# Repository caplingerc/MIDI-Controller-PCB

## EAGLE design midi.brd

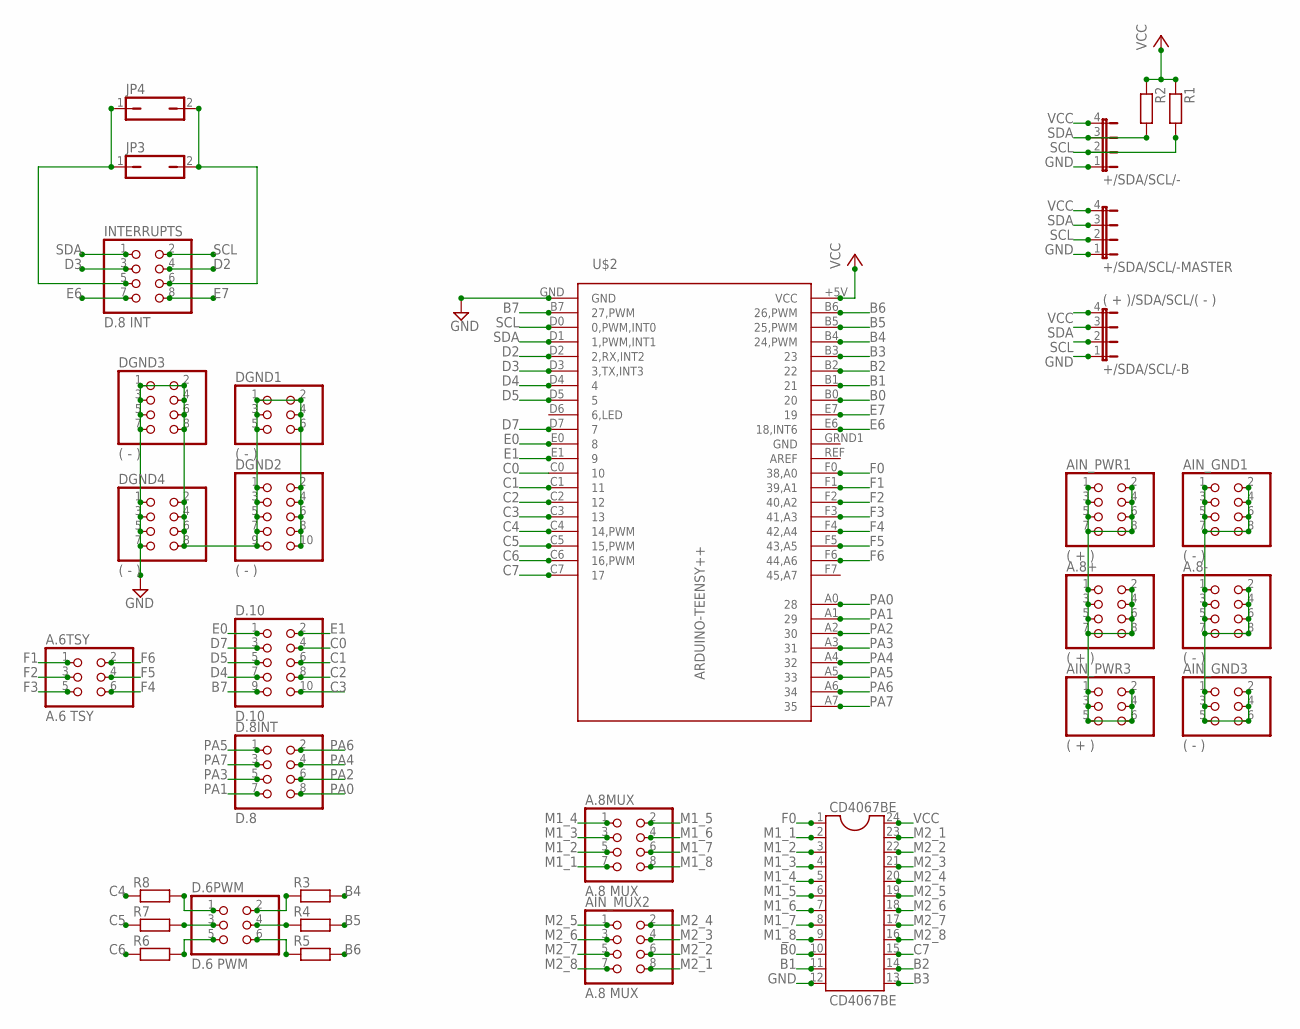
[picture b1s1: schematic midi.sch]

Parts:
+/SDA/SCL/-: JP4E; JP4
+/SDA/SCL/-B: ( + )/SDA/SCL/( - ); JP4
+/SDA/SCL/-MASTER: JP4E; JP4
A.6TSY: A.6 TSY; 2X03
A.8+: ( + ); 2X04
A.8-: ( - ); 2X04
A.8MUX: A.8 MUX; 2X04
AIN_GND1: ( - ); 2X04
AIN_GND3: ( - ); 2X03
AIN_MUX2: A.8 MUX; 2X04
AIN_PWR1: ( + ); 2X04
AIN_PWR3: ( + ); 2X03
CD4067BE: CD4067BE; DIL24-6
D.6PWM: D.6 PWM; 2X03
D.8INT: D.8; 2X04
D.10: D.10; 2X05
DGND1: ( - ); 2X03
DGND2: ( - ); 2X05
DGND3, DGND4: ( - ); 2X04
INTERRUPTS: D.8 INT; 2X04
JP3, JP4: JP1Q; JP1
R1, R2, R3, R4, R5, R6, R7, R8: 6MM-EU; R0207/3
U$2: ARDUINO-TEENSY++; TEENSY++

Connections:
B0: CD4067BE.10, U$2.B0 (20)
B1: CD4067BE.11, U$2.B1 (21)
B2: CD4067BE.14, U$2.B2 (22)
B3: CD4067BE.13, U$2.B3 (23)
B4: R3.2, U$2.B4 (24,PWM)
B5: R4.2, U$2.B5 (25,PWM)
B6: R5.2, U$2.B6 (26,PWM)
B7: D.10.9, U$2.B7 (27,PWM)
C0: D.10.4, U$2.C0 (10)
C1: D.10.6, U$2.C1 (11)
C2: D.10.8, U$2.C2 (12)
C3: D.10.10, U$2.C3 (13)
C4: R8.1, U$2.C4 (14,PWM)
C5: R7.1, U$2.C5 (15,PWM)
C6: R6.1, U$2.C6 (16,PWM)
C7: CD4067BE.15, U$2.C7 (17)
D2: INTERRUPTS.4, U$2.D2 (2,RX,INT2)
D3: INTERRUPTS.3, U$2.D3 (3,TX,INT3)
D4: D.10.7, U$2.D4 (4)
D5: D.10.5, U$2.D5 (5)
D7: D.10.3, U$2.D7 (7)
E0: D.10.1, U$2.E0 (8)
E1: D.10.2, U$2.E1 (9)
E6: INTERRUPTS.7, U$2.E6 (18,INT6)
E7: INTERRUPTS.8, U$2.E7 (19)
F0: CD4067BE.1, U$2.F0 (38,A0)
F1: A.6TSY.1, U$2.F1 (39,A1)
F2: A.6TSY.3, U$2.F2 (40,A2)
F3: A.6TSY.5, U$2.F3 (41,A3)
F4: A.6TSY.6, U$2.F4 (42,A4)
F5: A.6TSY.4, U$2.F5 (43,A5)
F6: A.6TSY.2, U$2.F6 (44,A6)
GND: +/SDA/SCL/-.1, +/SDA/SCL/-B.1, +/SDA/SCL/-MASTER.1, A.8-.1, A.8-.2, A.8-.3, A.8-.4, A.8-.5, A.8-.6, A.8-.7, A.8-.8, AIN_GND1.1, AIN_GND1.2, AIN_GND1.3, AIN_GND1.4, AIN_GND1.5, AIN_GND1.6, AIN_GND1.7, AIN_GND1.8, AIN_GND3.1, AIN_GND3.2, AIN_GND3.3, AIN_GND3.4, AIN_GND3.5, AIN_GND3.6, CD4067BE.12, DGND1.1, DGND1.2, DGND1.3, DGND1.4, DGND1.5, DGND1.6, DGND2.1, DGND2.2, DGND2.3, DGND2.4, DGND2.5, DGND2.6, DGND2.7, DGND2.8, DGND2.9, DGND2.10, DGND3.1, DGND3.2, DGND3.3, DGND3.4, DGND3.5, DGND3.6, DGND3.7, DGND3.8, DGND4.1, DGND4.2, DGND4.3, DGND4.4, DGND4.5, DGND4.6, DGND4.7, DGND4.8, U$2.GND, U$2.GRND1 (GND)
INT4: INTERRUPTS.6, JP3.2, JP4.2
INT5: INTERRUPTS.5, JP3.1, JP4.1
M1_1: A.8MUX.7, CD4067BE.2
M1_2: A.8MUX.5, CD4067BE.3
M1_3: A.8MUX.3, CD4067BE.4
M1_4: A.8MUX.1, CD4067BE.5
M1_5: A.8MUX.2, CD4067BE.6
M1_6: A.8MUX.4, CD4067BE.7
M1_7: A.8MUX.6, CD4067BE.8
M1_8: A.8MUX.8, CD4067BE.9
M2_1: AIN_MUX2.8, CD4067BE.23
M2_2: AIN_MUX2.6, CD4067BE.22
M2_3: AIN_MUX2.4, CD4067BE.21
M2_4: AIN_MUX2.2, CD4067BE.20
M2_5: AIN_MUX2.1, CD4067BE.19
M2_6: AIN_MUX2.3, CD4067BE.18
M2_7: AIN_MUX2.5, CD4067BE.17
M2_8: AIN_MUX2.7, CD4067BE.16
unnamed: D.6PWM.2, R3.1
unnamed: D.6PWM.4, R4.1
unnamed: D.6PWM.6, R5.1
unnamed: D.6PWM.5, R6.2
unnamed: D.6PWM.3, R7.2
unnamed: D.6PWM.1, R8.2
PA0: D.8INT.8, U$2.A0 (28)
PA1: D.8INT.7, U$2.A1 (29)
PA2: D.8INT.6, U$2.A2 (30)
PA3: D.8INT.5, U$2.A3 (31)
PA4: D.8INT.4, U$2.A4 (32)
PA5: D.8INT.1, U$2.A5 (33)
PA6: D.8INT.2, U$2.A6 (34)
PA7: D.8INT.3, U$2.A7 (35)
SCL: +/SDA/SCL/-.2, +/SDA/SCL/-B.2, +/SDA/SCL/-MASTER.2, INTERRUPTS.2, R1.2, U$2.D0 (0,PWM,INT0)
SDA: +/SDA/SCL/-.3, +/SDA/SCL/-B.3, +/SDA/SCL/-MASTER.3, INTERRUPTS.1, R2.2, U$2.D1 (1,PWM,INT1)
VCC: +/SDA/SCL/-.4, +/SDA/SCL/-B.4, +/SDA/SCL/-MASTER.4, A.8+.1, A.8+.2, A.8+.3, A.8+.4, A.8+.5, A.8+.6, A.8+.7, A.8+.8, AIN_PWR1.1, AIN_PWR1.2, AIN_PWR1.3, AIN_PWR1.4, AIN_PWR1.5, AIN_PWR1.6, AIN_PWR1.7, AIN_PWR1.8, AIN_PWR3.1, AIN_PWR3.2, AIN_PWR3.3, AIN_PWR3.4, AIN_PWR3.5, AIN_PWR3.6, CD4067BE.24, R1.1, R2.1, U$2.+5V (VCC)

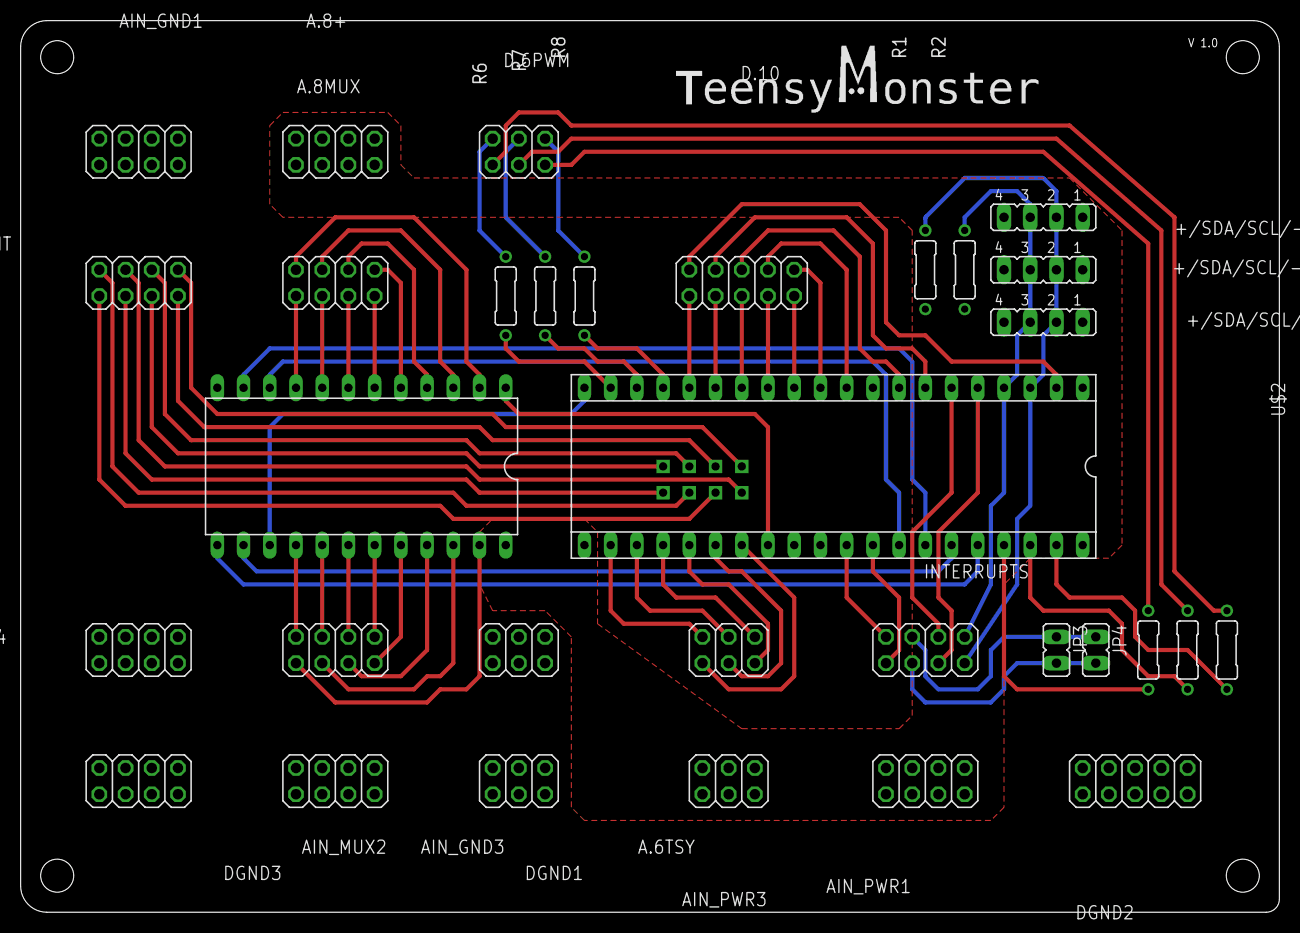
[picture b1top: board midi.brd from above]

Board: 2 copper layers, 121.9 x 86.4 mm, 32 parts (0 on the bottom side), 68 nets.
